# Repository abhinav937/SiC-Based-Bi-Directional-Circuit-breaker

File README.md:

# SiC-Based-Bi-Directional-E-Fuse

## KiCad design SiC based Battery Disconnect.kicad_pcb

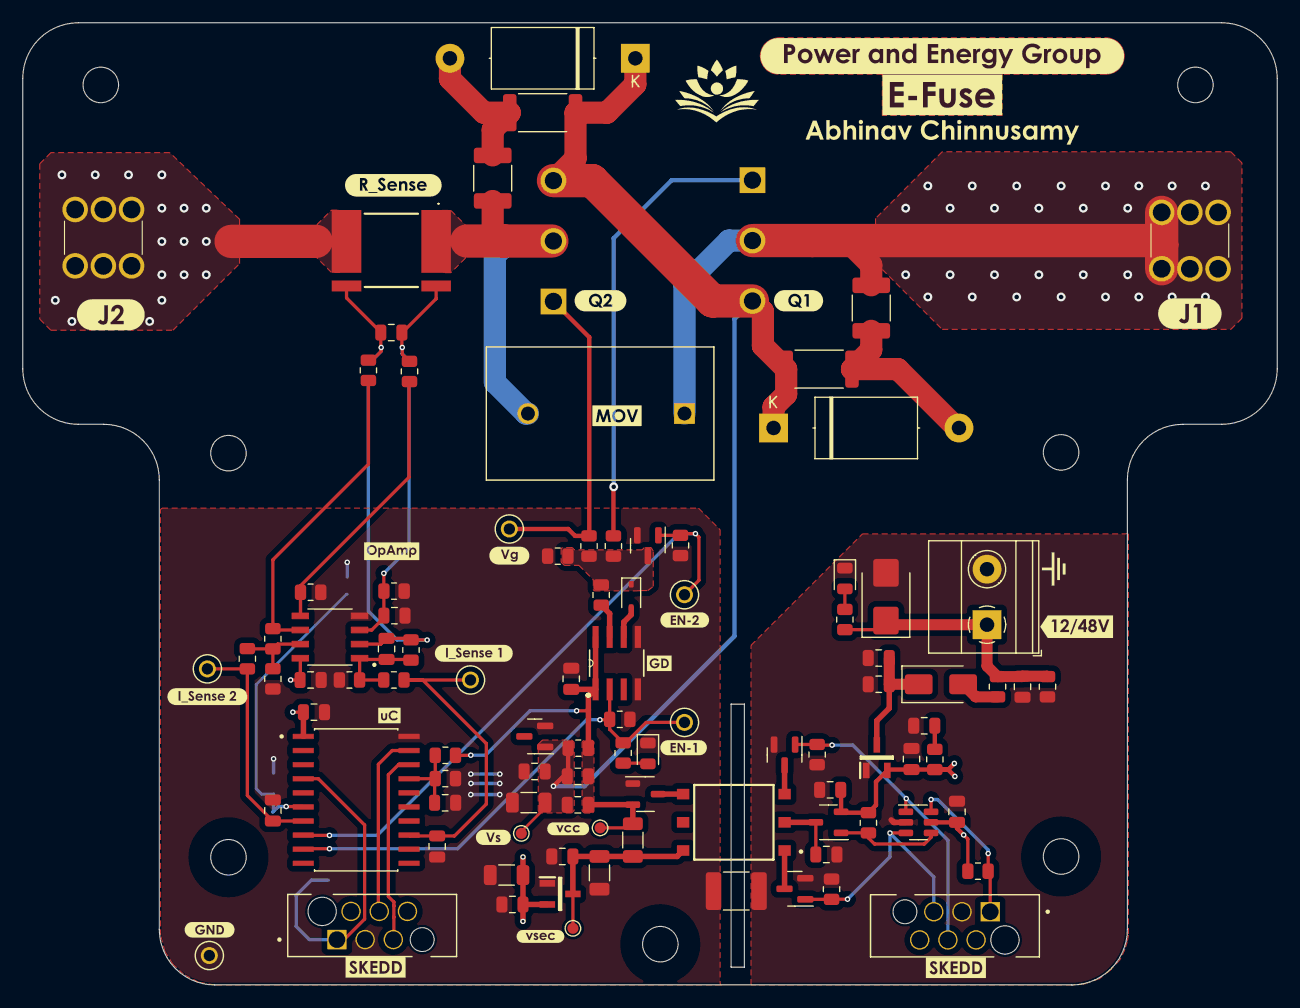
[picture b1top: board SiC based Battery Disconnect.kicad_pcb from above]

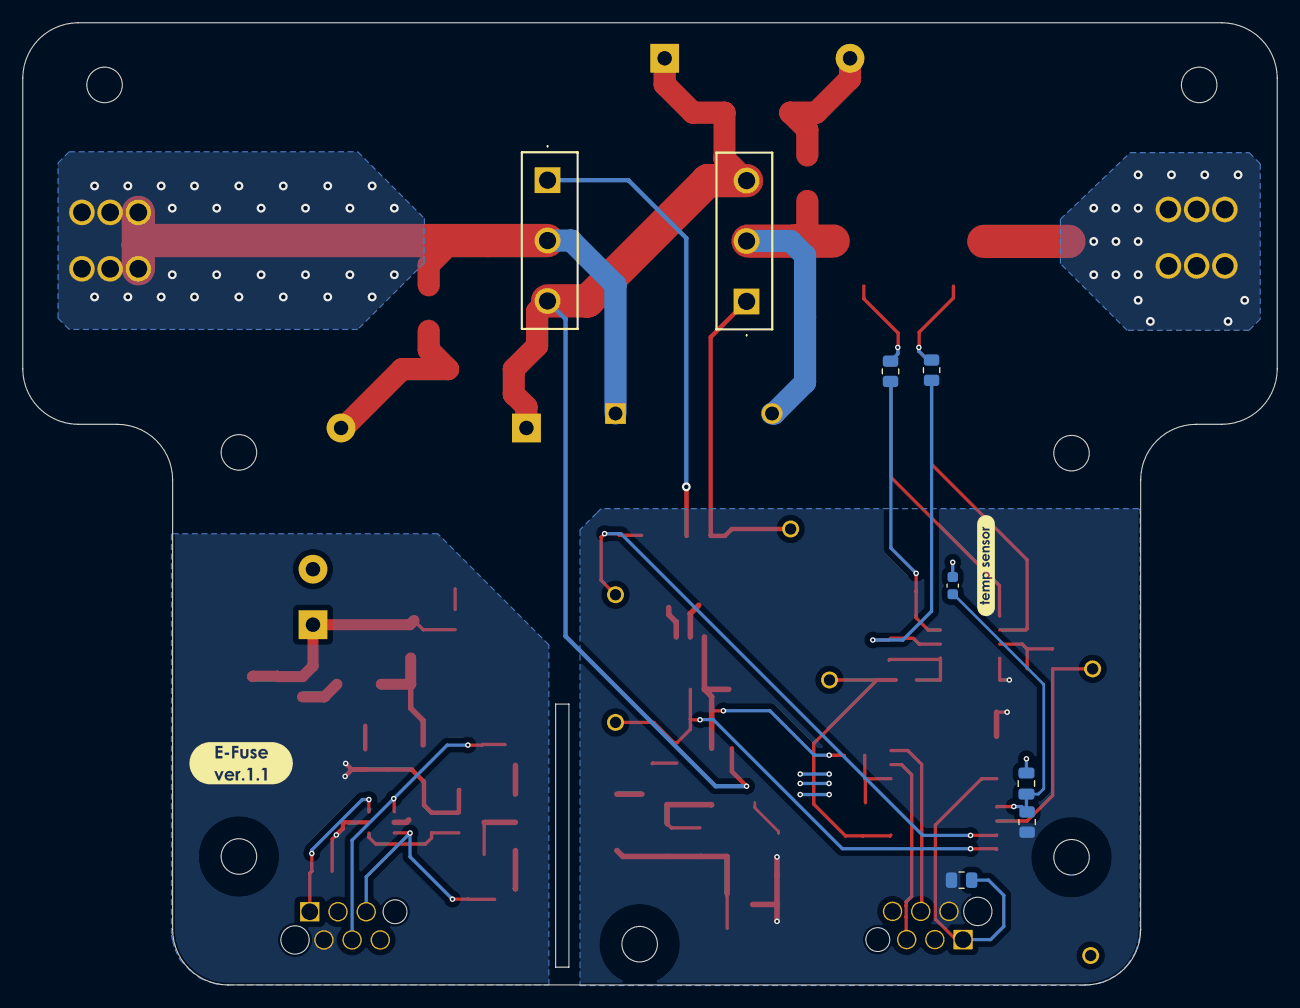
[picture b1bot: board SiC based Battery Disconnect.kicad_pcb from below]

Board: 2 copper layers, 113.0 x 86.7 mm, 136 parts (10 on the bottom side), 48 nets.

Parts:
C1: 100nF; C_0805_2012Metric
C2, C16: 4.7nF; C_1812_4532Metric
C3, C6, C17, C20, C21, C25, C26, C27, C28, C30: 0.1uF; C_0805_2012Metric
C4, C5: 10uF; C_1206_3216Metric
C7: 1uF; C_0805_2012Metric
C8: 4700pF; C_1812_4532Metric
C9, C12, C15: 100pF; C_0805_2012Metric
C10, C11, C13, C14, C18: 10000pF; C_0805_2012Metric
C19, C23: 10uF; C_0805_2012Metric
C22: 4.7uF; C_0805_2012Metric
C24, C29: 4.7uF; C_1206_3216Metric
D1: BAS70-04; SOT-23-3
D2, D6: LED; LED_0805_2012Metric
D3: SM6T68CA; D_SMB
D4: US1G; D_SMA
D5: BZX84C6V8; SOT-23
D7: BZX384-B22,115; D_SOD-323
D8, D9: D; D_DO-201AE_P12.70mm_Horizontal
H1, H2, H3, H4, H5, H6, H7: MountingHole; MountingHole_3.2mm_M3
IC2: PIC16F15345-I/SO; SOIC127P1030X265-20N
IC4, IC5: MCP1792T-5002H_CB; SOT95P255X145-3N
J1: Input; 7461057
J2: Output; 7461057
J3: 12V/48V supply; TerminalBlock_Phoenix_MKDS-1,5-2_1x02_P5.00mm_Horizontal
J5, J6: 490107670612; WURTH_490107670612
Q1, Q2: IMW120R014M1H
Q3, Q5, Q6: 2N7002BK,215; SOT-23
Q4: Si2333DS; SOT-23-3
R1, R2, R32: 20R; R_0805_2012Metric
R3: WSLP40261L000FEA
R4, R6, R7, R13, R30, R31, R35: 100k; R_0805_2012Metric
R5, R9, R11, R18, R25, R34: 10k; R_0805_2012Metric
R8: 10K; R_0805_2012Metric
R10, R12: 4.7k; R_0805_2012Metric
R14, R15, R19, R20, R22, R24, R33: 20k; R_0805_2012Metric
R16, R17: 1k; R_0805_2012Metric
R21, R23: 100R; R_0805_2012Metric
R26, R27: 18R; R_2512_6332Metric
R28: 0R; R_0805_2012Metric
R29: 4.7R; R_0805_2012Metric
RV1: Varistor; VARRB750W100L2050T1200H2800
T1: 760390014; 760390015
TH100: 10k; C_0603_1608Metric
TP1, TP2, TP6, TP7, TP9: 5001; KEYSTONE_5001
TP3, TP4, TP8: TestPoint; TestPoint_Pad_D1.0mm
TP5: 5001/TestPoint; KEYSTONE_5001
U1: PIC10F322-IOT; SOT-23-6
U2: MCP6022; SOIC127P599X175-8N
U4: TC4432VOA; SOIC127P600X175-8N
kibuzzard-64D0ED59, kibuzzard-64D0ED59#2: G***; kibuzzard-64D0ED59
kibuzzard-651F86C6: G***; kibuzzard-651F86C6
kibuzzard-651F886F: G***; kibuzzard-651F886F
kibuzzard-6557C38A: G***; kibuzzard-6557C38A
kibuzzard-65082C7F: G***; kibuzzard-65082C7F
kibuzzard-65082D1D: G***; kibuzzard-65082D1D
kibuzzard-65082D52: G***; kibuzzard-65082D52
kibuzzard-65082FCA: G***; kibuzzard-65082FCA
kibuzzard-65082FE1: G***; kibuzzard-65082FE1
kibuzzard-650825C2: G***; kibuzzard-650825C2
kibuzzard-650825F1: G***; kibuzzard-650825F1
kibuzzard-650830BB: G***; kibuzzard-650830BB
kibuzzard-650830F5: G***; kibuzzard-650830F5
kibuzzard-650834CF: G***; kibuzzard-650834CF
kibuzzard-650835E3: G***; kibuzzard-650835E3
kibuzzard-6508239C: G***; kibuzzard-6508239C
kibuzzard-6508248A: G***; kibuzzard-6508248A
kibuzzard-6508304F: G***; kibuzzard-6508304F
kibuzzard-6508305D: G***; kibuzzard-6508305D
kibuzzard-6508313B: G***; kibuzzard-6508313B
kibuzzard-6508355A: G***; kibuzzard-6508355A
kibuzzard-6508356A: G***; kibuzzard-6508356A
kibuzzard-65082383: G***; kibuzzard-65082383
kibuzzard-65082582: G***; kibuzzard-65082582
kibuzzard-65083125: G***; kibuzzard-65083125

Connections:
BATT+(12V-48V): C18.2, D3.1 (A1), J3.1, R11.1, R29.1, R34.1
DRIVER_EN1: IC2.9 (RC7), R10.1, R30.2, TP1.TP, U4.2 (IN)
DRIVER_EN2: IC2.8 (RC6), Q6.1 (G), R35.2, TP2.TP
Earth: C3.2, C7.2, C8.1, C17.1, C18.1, C19.1, C20.1, C21.1, C22.1, D3.2 (A2), D6.1 (K), IC5.1 (GND), J3.2, J5.3, Q3.2 (S), Q5.2 (S), R4.2, R7.2, R11.2, U1.2 (VSS)
GND: C1.2, C5.2, C6.1, C8.2, C9.2, C10.2, C11.2, C12.2, C13.2, C24.1, C25.1, C27.1, C28.1, C29.1, C30.2, D1.1 (K), D2.1 (K), D5.2 (A), IC2.20 (VSS), IC4.1 (GND), J6.3, Q6.2 (S), R9.1, R19.1, R20.1, R22.1, R25.1, R30.1, R31.1, R35.1, TH100.2, TP5.TP, U2.4 (V-), U4.4 (GND_2), U4.5 (GND)
I_SENSE_ANB4: C13.1, IC2.13 (RB4), R23.1, TP6.TP
I_SENSE_C3IN1-: C12.1, IC2.7 (RC3), R21.1, TP7.TP
I_sense+: C15.1, R3.4, R14.1, R16.1
I_sense-: C15.2, R3.3, R15.1, R17.1
unnamed: C14.2, R22.2, R23.2, R24.2, U2.1
unnamed: C22.2, R28.2
unnamed: D1.3 (A), T1.4
unnamed: D2.2 (A), R10.2
unnamed: D4.2 (A), R29.2
unnamed: C19.2, C20.2, D4.1 (K), IC5.3 (VIN)
unnamed: D6.2 (A), R34.2
unnamed: D7.2 (A), U4.6 (*OUT_2)
unnamed: D7.1 (K), Q6.3 (D), R1.1, R2.1, R31.2, R32.2
unnamed: C16.2, D8.2 (A), R27.1
unnamed: C2.2, D9.2 (A), R26.1
unnamed: C9.1, IC2.17 (RA2), R9.2, R13.1
unnamed: C10.1, IC2.6 (RC4), R12.2, TH100.1
unnamed: J2.1, J2.2, J2.3, J2.4, J2.5, J2.6, R3.2
unnamed: C2.1, J1.1, J1.2, J1.3, J1.4, J1.5, J1.6, Q1.2 (D), RV1.1
unnamed: Q1.1 (G), R1.2
unnamed: C16.1, Q2.2 (D), R3.1, RV1.2
unnamed: Q2.1 (G), R2.2, TP9.TP
unnamed: Q3.3 (D), T1.3
unnamed: C7.1, Q4.3 (D), T1.2
unnamed: Q4.1 (G), R6.1, U1.4 (RA2)
unnamed: Q5.3 (D), T1.1
unnamed: R18.2, R20.2, R21.2, U2.7
unnamed: C11.1, R16.2, R19.2, U2.3 (+)
unnamed: C14.1, R17.2, R24.1, U2.2 (-)
unnamed: R14.2, R25.2, U2.5 (+)
unnamed: R15.2, R18.1, U2.6 (-)
unnamed: R32.1, U4.7 (*OUT)
RA0: IC2.19 (RA0/ICSPDAT), J6.4
RA0_{lv}: J5.4, Q3.1 (G), R4.1, U1.1 (RA0)
RA1: IC2.18 (RA1/ICSPCLK), J6.5
RA1_{lv}: J5.5, Q5.1 (G), R7.1, U1.3 (RA1)
RA3: IC2.4 (~MCLR/VPP/RA3), J6.1, R5.1
RA3_{lv}: J5.1, R8.2, U1.6 (RA3)
VCC: C1.1, C4.1, C23.1, C26.2, D1.2 (K), R13.2, R33.1, TP8.1, U4.1 (VDD_2), U4.8 (VDD)
VDDHV: C6.2, C28.2, C29.2, C30.1, IC2.1 (VDD), IC4.2 (VOUT), J6.2, R5.2, R12.1, U2.8 (V+)
VDDLV: C3.1, C17.2, C21.2, IC5.2 (VOUT), J5.2, Q4.2 (S), R6.2, R8.1, R28.1, U1.5 (VDD)
VSEC: C4.2, C5.1, C27.2, IC4.3 (VIN), T1.6, TP3.1
VSOURCE: C23.2, C24.2, C25.2, C26.1, D5.1 (K), D8.1 (K), D9.1 (K), Q1.3 (S), Q2.3 (S), R26.2, R27.2, R33.2, TP4.1

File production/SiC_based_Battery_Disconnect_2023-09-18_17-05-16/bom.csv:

Designator,Footprint,Quantity,Value,LCSC Part #
C1,0805,1,100nF,
"C10, C11, C13, C14, C18",0805,5,10000pF,
"C12, C15, C9",0805,3,100pF,
"C16, C2",1812,2,4.7nF,
"C17, C20, C21, C25, C26, C27, C28, C3, C6",0805,9,0.1uF,
"C19, C23",0805,2,10uF,
C22,0805,1,4.7uF,
"C24, C29",1206,2,4.7uF,
"C4, C5",1206,2,10uF,
C7,0805,1,1uF,
C8,1812,1,4700pF,
D1,SOT-23-3,1,BAS70-04,
"D2, D6",0805,2,LED,
D3,D_SMB,1,SM6T39A,
D4,D_SMA,1,US1G,
D5,SOT-23,1,BZX84C6V8,
D7,D_SOD-323,1,"BZX384-B22,115",
"D8, D9",D_DO-201AE_P12.70mm_Horizontal,2,D,
"H1, H2, H3, H4, H5, H6, H7",MountingHole_3.2mm_M3,7,MountingHole,
IC2,SOP65P780X200-20N,1,PIC16F15345T-E_SSVAO,
"IC4, IC5",SOT95P255X145-3N,2,MCP1792T-5002H_CB,
J1,7461057,1,Input,
J2,7461057,1,Output,
J3,"TerminalBlock_Phoenix_MKDS-1,5-2_1x02_P5.00mm_Horizontal",1,12V supply,
"J5, J6",WURTH_490107670612,2,490107670612,
"Q1, Q2",IMW120R014M1H,2,IMW120R014M1H,
"Q3, Q5, Q6",SOT-23,3,"2N7002BK,215",
Q4,SOT-23-3,1,Si2333DS,
"R1, R2, R32",0805,3,20R,
"R10, R12",0805,2,4.7k,
"R11, R18, R25, R34, R5, R8, R9",0805,7,10k,
"R13, R30, R31, R35, R4, R6, R7",0805,7,100k,
"R14, R15, R19, R20, R22, R24, R33",0805,7,20k,
"R16, R17",0805,2,1k,
"R21, R23",0805,2,100R,
"R26, R27",2512,2,18R,
R28,0805,1,0R,
R29,0805,1,4.7R,
R3,WSLP40261L000FEA,1,WSLP40261L000FEA,
RV1,VARRB750W100L2050T1200H2800,1,Varistor,
T1,760390015,1,760390014,
TH100,0603,1,10k,
"TP1, TP2, TP5, TP6, TP7, TP9",KEYSTONE_5001,6,5001,
"TP3, TP4, TP8",TestPoint_Pad_D1.0mm,3,TestPoint,
U1,SOT-23-6,1,PIC10F322-IOT,
U2,TSSOP-8_4.4x3mm_P0.65mm,1,MCP6022,
U4,SOIC127P600X175-8N,1,TC4432VOA,TC4432VOA

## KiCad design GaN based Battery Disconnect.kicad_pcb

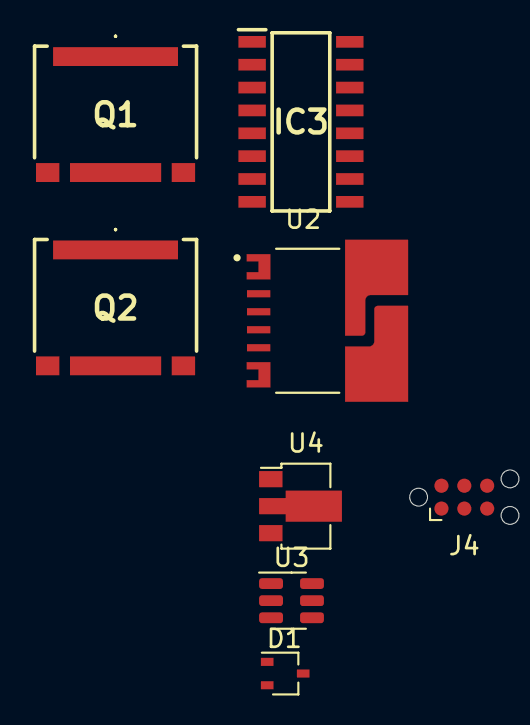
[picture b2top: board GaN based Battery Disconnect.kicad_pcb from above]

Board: 2 copper layers, 8 parts (0 on the bottom side), 9 nets, no tracks yet.

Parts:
D1: BAT54SW; SOT-323_SC-70
IC3: 2EDF7275F; SOIC127P600X175-16N
J4: Conn_ARM_SWD_TagConnect_TC2030-NL; Tag-Connect_TC2030-IDC-NL_2x03_P1.27mm_Vertical
Q1, Q2: GS-065-060-5-T-A; GS0650605TA
U2: TLI4971A050T5UE0001XUMA1; IC_TLE4971A050T5UE0001XUMA1
U3: SN6505BDBV; SOT-23-6
U4: L78L09_SOT89; SOT-89-3

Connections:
0V_a: Q1.3 (S), Q2.3 (S)
+3V3: IC3.3 (VDDI), J4.2 (SWDIO)
+5V: U3.2 (VCC), U3.5 (EN)
+6V_a: IC3.16 (VDDA), U4.1 (OUT)
-3v_a: D1.1 (A), IC3.14 (GNDA), U4.2 (GND)
BATT-: U3.4 (GND), U3.6 (CLK)
GND: IC3.4 (GNDI), IC3.8 (SLDON), J4.3 (~RESET), U2.2 (GND)
unnamed: D1.2 (K), U4.3 (IN)
unnamed: Q2.1 (D), U2.8 (IP+)

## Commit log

2023-08-11 face to face switches design
    with no MOVs and all other present
2023-09-07 updated the design
2023-09-15 design update
2023-10-04 Design with footprint error
2024-04-02 Final Design
